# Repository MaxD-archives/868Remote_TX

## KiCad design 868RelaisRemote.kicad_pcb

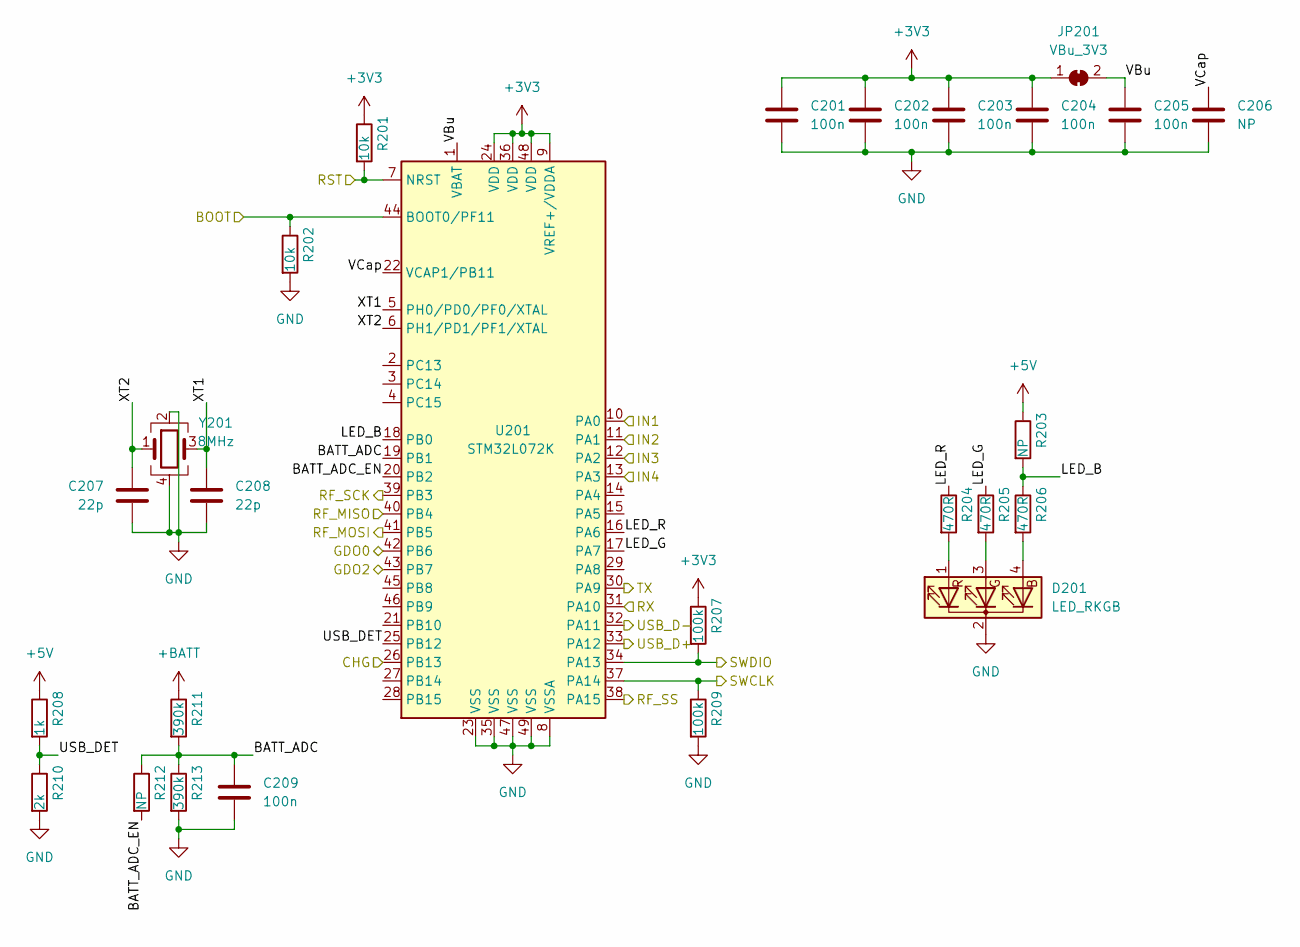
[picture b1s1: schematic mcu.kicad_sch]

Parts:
C201, C202, C203, C204, C205, C209: 100n; C_0603_1608Metric
C206: NP; C_0603_1608Metric
C207, C208: 22p; C_0603_1608Metric
D201: LED_RKGB; LED_D5.0mm-4_RGB
JP201: VBu_3V3; SolderJumper-2_P1.3mm_Bridged_RoundedPad1.0x1.5mm
R201, R202: 10k; R_0603_1608Metric
R203, R212: NP; R_0603_1608Metric
R204, R205, R206: 470R; R_0603_1608Metric
R207, R209: 100k; R_0603_1608Metric
R208: 1k; R_0603_1608Metric
R210: 2k; R_0603_1608Metric
R211, R213: 390k; R_0603_1608Metric
U201: STM32L072K; LQFPN-48_7x7_multi
Y201: 8MHz; Crystal_SMD_3225-4Pin_3.2x2.5mm

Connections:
+3V3: C201.1, C202.1, C203.1, C204.1, JP201.1 (A), R201.1, R207.1, U201.9 (VREF+/VDDA), U201.24 (VDD), U201.36 (VDD), U201.48 (VDD); also elsewhere on the board
+5V: R203.1, R208.1; also elsewhere on the board
+BATT: R211.1; also elsewhere on the board
/Connectors/BOOT: R202.1, U201.44 (BOOT0/PF11); also elsewhere on the board
/Connectors/IN1: U201.10 (PA0); also elsewhere on the board
/Connectors/IN2: U201.11 (PA1); also elsewhere on the board
/Connectors/IN3: U201.12 (PA2); also elsewhere on the board
/Connectors/IN4: U201.13 (PA3); also elsewhere on the board
/Connectors/RST: R201.2, U201.7 (NRST); also elsewhere on the board
/Connectors/RX: U201.31 (PA10); also elsewhere on the board
/Connectors/SWCLK: R209.1, U201.37 (PA14); also elsewhere on the board
/Connectors/SWDIO: R207.2, U201.34 (PA13); also elsewhere on the board
/Connectors/TX: U201.30 (PA9); also elsewhere on the board
/Connectors/USBD+: U201.33 (PA12); also elsewhere on the board
/Connectors/USBD-: U201.32 (PA11); also elsewhere on the board
/MCU/BATT_ADC: C209.1, R211.2, R212.1, R213.1, U201.19 (PB1)
/MCU/BATT_ADC_EN: R212.2, U201.20 (PB2)
/MCU/CHG: U201.26 (PB13); also elsewhere on the board
/MCU/GDO0: U201.42 (PB6); also elsewhere on the board
/MCU/GDO2: U201.43 (PB7); also elsewhere on the board
/MCU/LED_B: R203.2, R206.1, U201.18 (PB0)
/MCU/LED_G: R205.1, U201.17 (PA7)
/MCU/LED_R: R204.1, U201.16 (PA6)
/MCU/RF_MISO: U201.40 (PB4); also elsewhere on the board
/MCU/RF_MOSI: U201.41 (PB5); also elsewhere on the board
/MCU/RF_SCK: U201.39 (PB3); also elsewhere on the board
/MCU/RF_SS: U201.38 (PA15); also elsewhere on the board
/MCU/USB_DET: R208.2, R210.1, U201.25 (PB12)
/MCU/VBu: C205.1, JP201.2 (B), U201.1 (VBAT)
/MCU/VCap: C206.1, U201.22 (VCAP1/PB11)
/MCU/XT1: C208.2, U201.5 (PH0/PD0/PF0/XTAL), Y201.3
/MCU/XT2: C207.2, U201.6 (PH1/PD1/PF1/XTAL), Y201.1
GND: C201.2, C202.2, C203.2, C204.2, C205.2, C206.2, C207.1, C208.1, C209.2, D201.2 (K), R202.2, R209.2, R210.2, R213.2, U201.8 (VSSA), U201.23 (VSS), U201.35 (VSS), U201.47 (VSS), U201.49 (VSS), Y201.2, Y201.4; also elsewhere on the board
unnamed: D201.1 (RA), R204.2
unnamed: D201.3 (GA), R205.2
unnamed: D201.4 (BA), R206.2

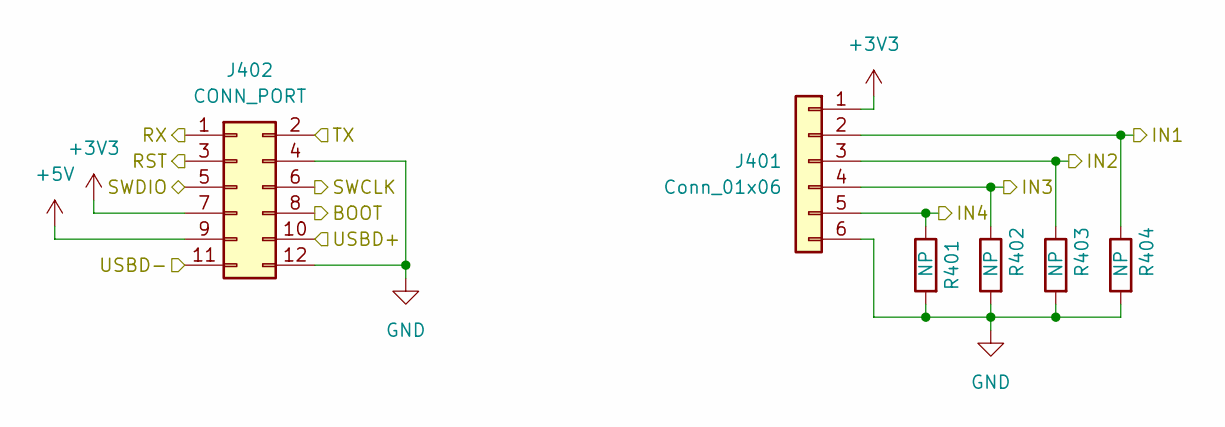
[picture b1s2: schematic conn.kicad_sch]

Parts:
J401: Conn_01x06; JST_XH_B6B-XH-A_1x06_P2.50mm_Vertical
J402: CONN_PORT; IDC-Header_2x06_P2.54mm_Vertical
R401, R402, R403, R404: NP; R_0603_1608Metric

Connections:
+3V3: J401.1, J402.7; also elsewhere on the board
+5V: J402.9; also elsewhere on the board
/Connectors/BOOT: J402.8; also elsewhere on the board
/Connectors/IN1: J401.2, R404.1; also elsewhere on the board
/Connectors/IN2: J401.3, R403.1; also elsewhere on the board
/Connectors/IN3: J401.4, R402.1; also elsewhere on the board
/Connectors/IN4: J401.5, R401.1; also elsewhere on the board
/Connectors/RST: J402.3; also elsewhere on the board
/Connectors/RX: J402.1; also elsewhere on the board
/Connectors/SWCLK: J402.6; also elsewhere on the board
/Connectors/SWDIO: J402.5; also elsewhere on the board
/Connectors/TX: J402.2; also elsewhere on the board
/Connectors/USBD+: J402.10; also elsewhere on the board
/Connectors/USBD-: J402.11; also elsewhere on the board
GND: J401.6, J402.4, J402.12, R401.2, R402.2, R403.2, R404.2; also elsewhere on the board

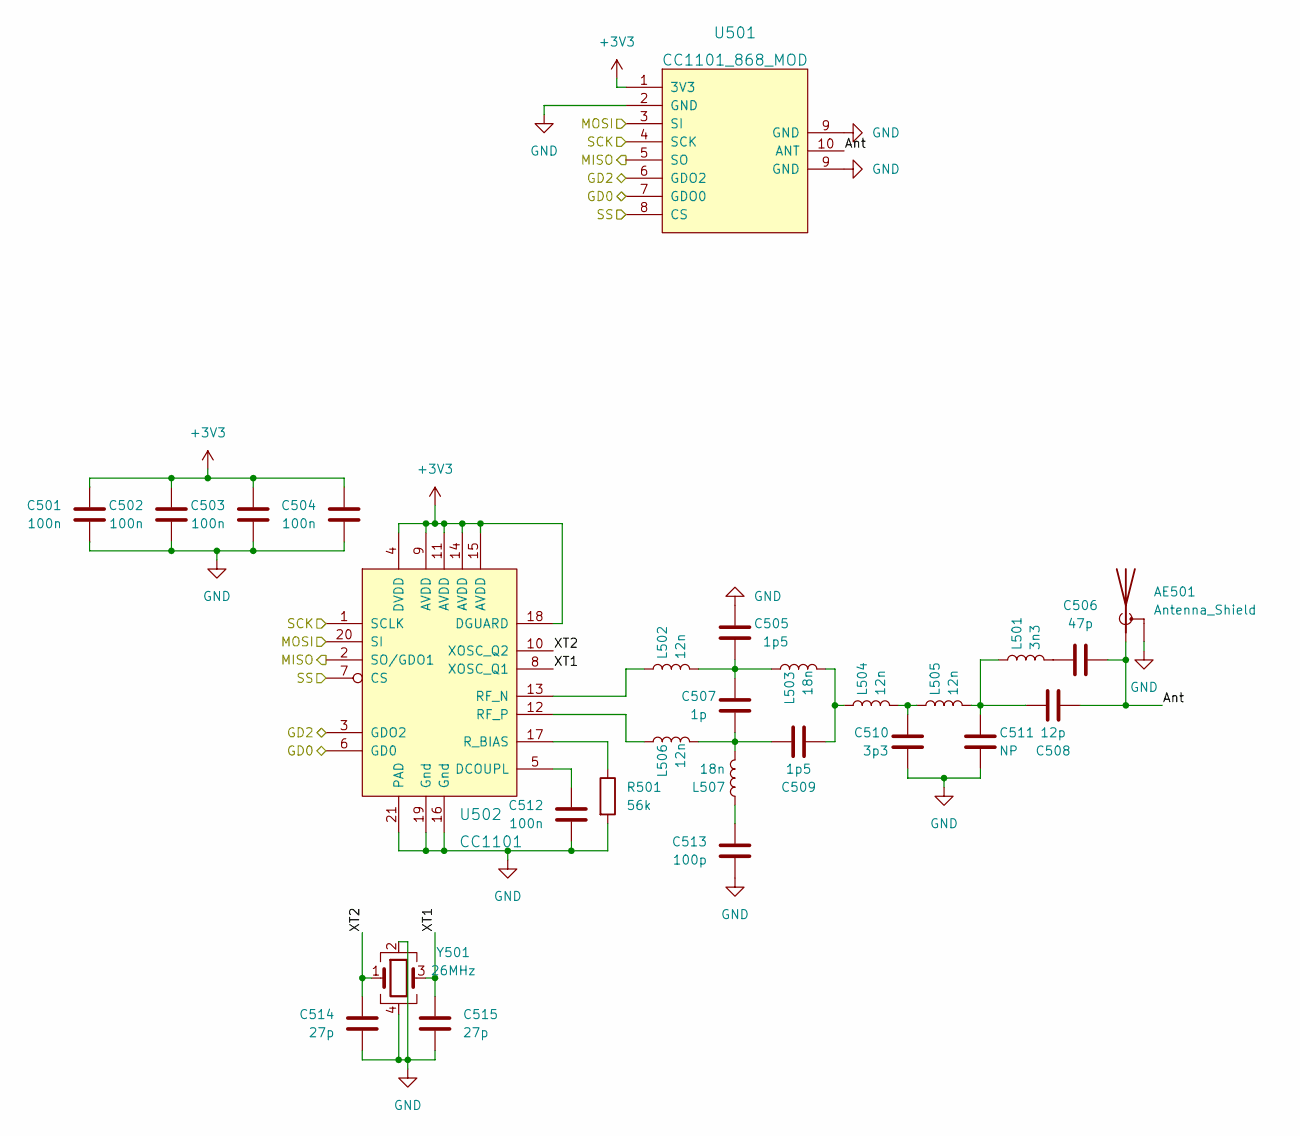
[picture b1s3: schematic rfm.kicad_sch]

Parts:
AE501: Antenna_Shield; U.FL_Molex_MCRF_73412-0110_Vertical
C501, C502, C503, C504, C512: 100n; C_0603_1608Metric
C505, C509: 1p5; C_0603_1608Metric
C506: 47p; C_0603_1608Metric
C507: 1p; C_0603_1608Metric
C508: 12p; C_0603_1608Metric
C510: 3p3; C_0603_1608Metric
C511: NP; C_0603_1608Metric
C513: 100p; C_0603_1608Metric
C514, C515: 27p; C_0603_1608Metric
L501: 3n3; L_0603_1608Metric
L502, L504, L505, L506: 12n; L_0603_1608Metric
L503, L507: 18n; L_0603_1608Metric
R501: 56k; R_0603_1608Metric
U501: CC1101_868_MOD; CC1101_MOD868
U502: CC1101; QFN-20-1EP_4x4mm_P0.5mm_EP2.5x2.5mm
Y501: 26MHz; Crystal_SMD_3225-4Pin_3.2x2.5mm

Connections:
+3V3: C501.2, C502.2, C503.2, C504.2, U501.1 (3V3), U502.4 (DVDD), U502.9 (AVDD), U502.11 (AVDD), U502.14 (AVDD), U502.15 (AVDD), U502.18 (DGUARD); also elsewhere on the board
/MCU/GDO0: U501.7 (GDO0), U502.6 (GD0); also elsewhere on the board
/MCU/GDO2: U501.6 (GDO2), U502.3 (GDO2); also elsewhere on the board
/MCU/RF_MISO: U501.5 (SO), U502.2 (SO/GDO1); also elsewhere on the board
/MCU/RF_MOSI: U501.3 (SI), U502.20 (SI); also elsewhere on the board
/MCU/RF_SCK: U501.4 (SCK), U502.1 (SCLK); also elsewhere on the board
/MCU/RF_SS: U501.8 (CS), U502.7 (CS); also elsewhere on the board
/RF-Module/Ant: AE501.1 (A), C506.2, C508.2, U501.10 (ANT)
/RF-Module/XT1: C515.2, U502.8 (XOSC_Q1), Y501.3
/RF-Module/XT2: C514.2, U502.10 (XOSC_Q2), Y501.1
GND: AE501.2 (Shield), C501.1, C502.1, C503.1, C504.1, C505.1, C510.1, C511.1, C512.1, C513.1, C514.1, C515.1, R501.2, U501.2 (GND), U501.9 (GND), U502.16 (Gnd), U502.19 (Gnd), U502.21 (PAD), Y501.2, Y501.4; also elsewhere on the board
unnamed: C505.2, C507.1, L502.2, L503.1
unnamed: C506.1, L501.2
unnamed: C507.2, C509.1, L506.2, L507.2
unnamed: C508.1, C511.2, L501.1, L505.2
unnamed: C509.2, L503.2, L504.1
unnamed: C510.2, L504.2, L505.1
unnamed: C512.2, U502.5 (DCOUPL)
unnamed: C513.2, L507.1
unnamed: L502.1, U502.13 (RF_N)
unnamed: L506.1, U502.12 (RF_P)
unnamed: R501.1, U502.17 (R_BIAS)

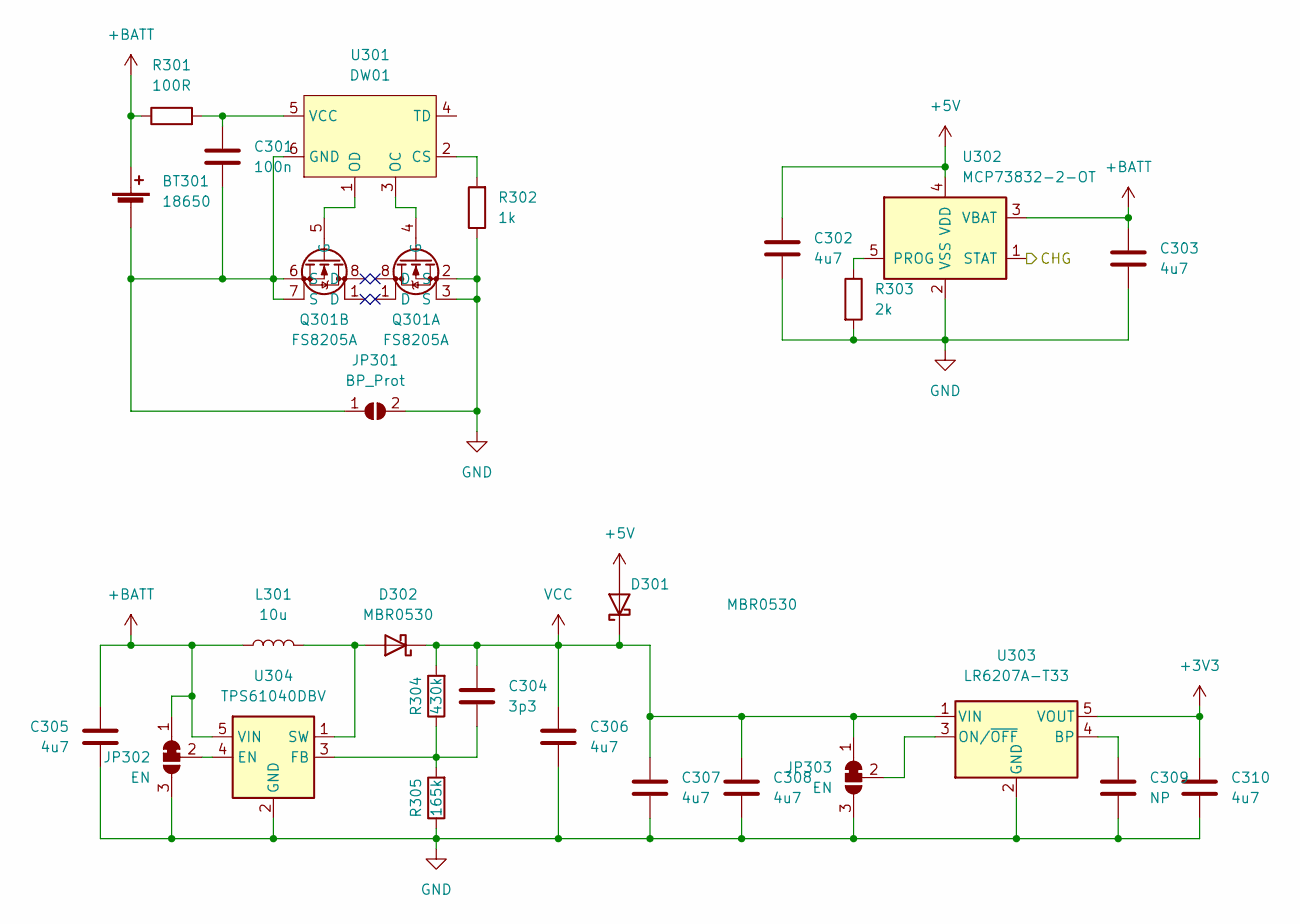
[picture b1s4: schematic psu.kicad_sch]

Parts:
BT301: 18650; Keystone_54_18650
C301: 100n; C_0603_1608Metric
C302, C303, C305, C306, C307, C308, C310: 4u7; C_0805_2012Metric
C304: 3p3; C_0603_1608Metric
C309: NP; C_0603_1608Metric
D301, D302: MBR0530; D_SOD-123
JP301: BP_Prot; SolderJumper-2_P1.3mm_Open_RoundedPad1.0x1.5mm
JP302, JP303: EN; SolderJumper-3_P1.3mm_Bridged12_RoundedPad1.0x1.5mm
L301: 10u; L_Wuerth_MAPI-3015
Q301: FS8205A; TSSOP-8_4.4x3mm_P0.65mm
R301: 100R; R_0603_1608Metric
R302: 1k; R_0603_1608Metric
R303: 2k; R_0603_1608Metric
R304: 430k; R_0603_1608Metric
R305: 165k; R_0603_1608Metric
U301: DW01; SOT-23-6_Handsoldering
U302: MCP73832-2-OT; SOT-23-5
U303: LR6207A-T33; SOT-23-5
U304: TPS61040DBV; SOT-23-5

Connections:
+3V3: C310.1, U303.5 (VOUT); also elsewhere on the board
+5V: C302.1, D301.2 (A), U302.4 (VDD); also elsewhere on the board
+BATT: BT301.1 (+), C303.1, C305.2, JP302.1 (A), L301.1, R301.1, U302.3 (VBAT), U304.5 (VIN); also elsewhere on the board
/MCU/CHG: U302.1 (STAT); also elsewhere on the board
GND: C302.2, C303.2, C305.1, C306.2, C307.2, C308.2, C309.2, C310.2, JP301.2 (B), JP302.3 (B), JP303.3 (B), Q301.2 (S), Q301.3 (S), R302.1, R303.2, R305.1, U302.2 (VSS), U303.2 (GND), U304.2 (GND); also elsewhere on the board
unnamed: BT301.2 (-), C301.2, JP301.1 (A), Q301.6 (S), Q301.7 (S), U301.6 (GND)
unnamed: C301.1, R301.2, U301.5 (VCC)
unnamed: C304.2, R304.1, R305.2, U304.3 (FB)
unnamed: C309.1, U303.4 (BP)
unnamed: D302.2 (A), L301.2, U304.1 (SW)
unnamed: JP302.2 (C), U304.4 (EN)
unnamed: JP303.2 (C), U303.3 (ON/~OFF)
unnamed: Q301.4 (G), U301.3 (OC)
unnamed: Q301.5 (G), U301.1 (OD)
unnamed: R302.2, U301.2 (CS)
unnamed: R303.1, U302.5 (PROG)
VCC: C304.1, C306.1, C307.1, C308.1, D301.1 (K), D302.1 (K), JP303.1 (A), R304.2, U303.1 (VIN)

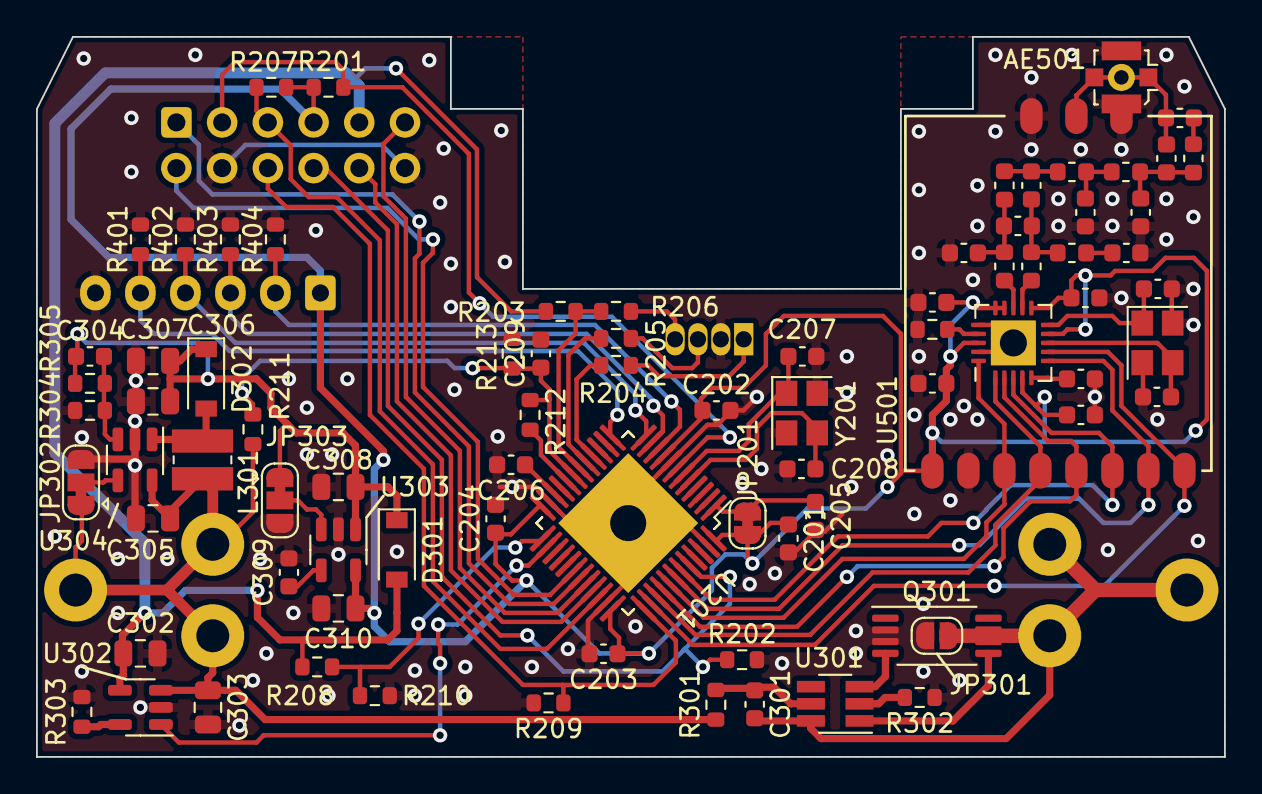
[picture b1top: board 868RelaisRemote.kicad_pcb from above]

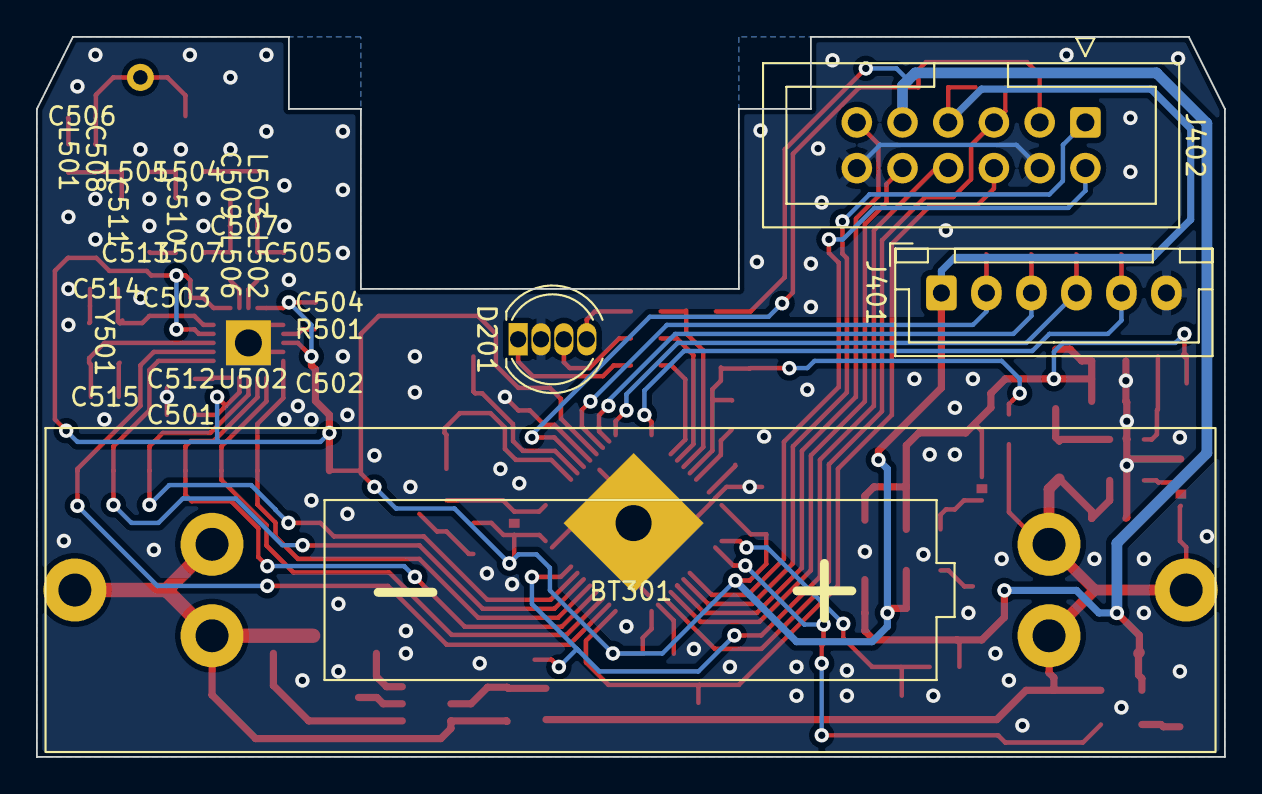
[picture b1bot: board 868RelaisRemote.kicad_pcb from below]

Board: 2 copper layers, 66.0 x 40.0 mm, 86 parts (4 on the bottom side), 62 nets.

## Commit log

2024-10-25 Initial upload
